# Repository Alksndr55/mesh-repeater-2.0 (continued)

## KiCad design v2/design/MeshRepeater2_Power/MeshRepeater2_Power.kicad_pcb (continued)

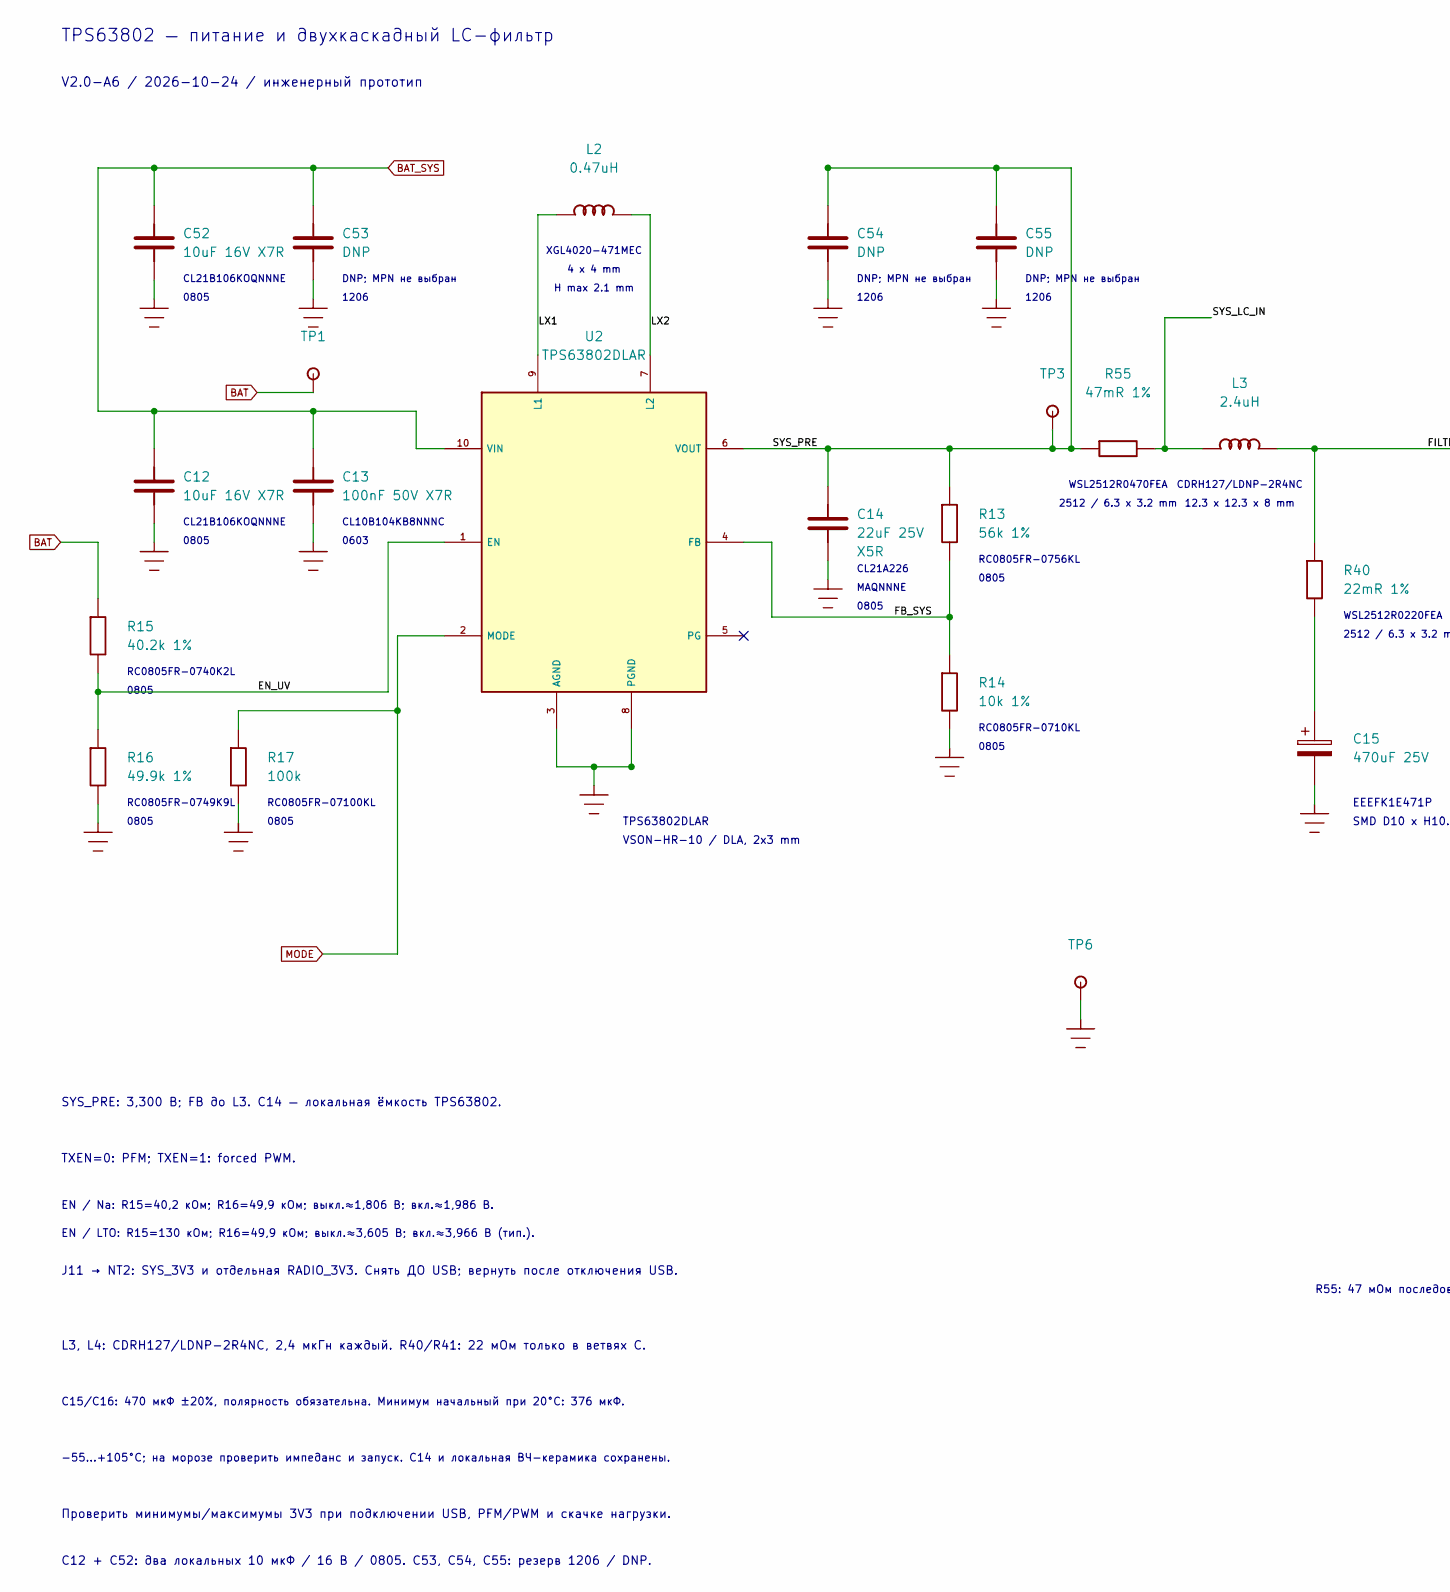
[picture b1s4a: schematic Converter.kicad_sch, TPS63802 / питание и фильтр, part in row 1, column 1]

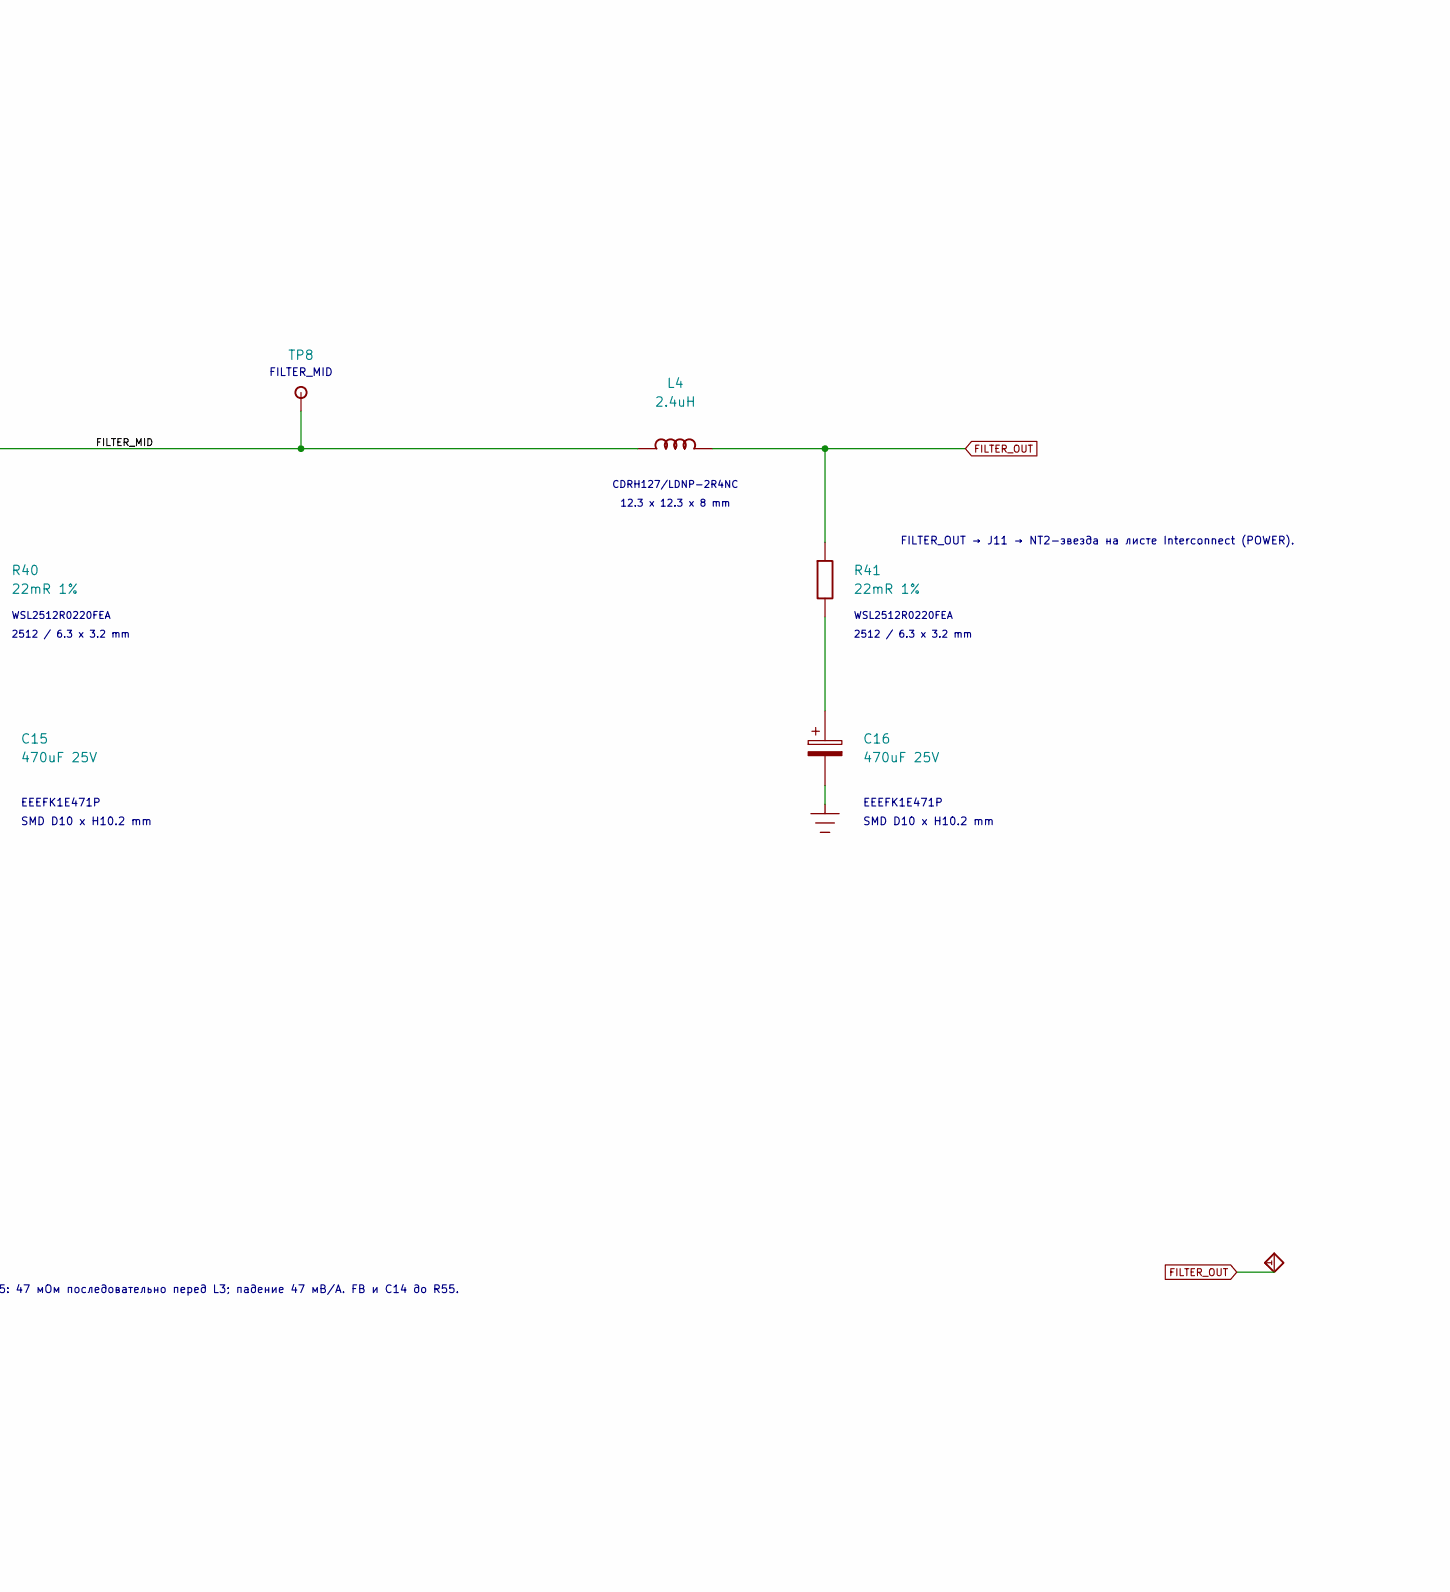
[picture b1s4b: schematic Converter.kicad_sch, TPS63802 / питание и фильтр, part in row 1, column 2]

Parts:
C12: 10uF 16V X7R; C_0805_2012Metric__V2_C12; MPN CL21B106KOQNNNE
C13: 100nF 50V X7R; C_0805_2012Metric; MPN CL21B104KBCNNNC
C14: 22uF 25V X5R; C_0805_2012Metric__V2_C14; MPN CL21A226MAQNNNE
C15, C16: 470uF 25V; CP_Elec_10x10.2; MPN EEEFK1E471P
C52: 10uF 16V X7R; C_0805_2012Metric__V2_C52; MPN CL21B106KOQNNNE
C53: DNP; C_1206_3216Metric__V2_C53
C54: DNP; C_1206_3216Metric__V2_C54
C55: DNP; C_1206_3216Metric__V2_C55
L2: 0.47uH; L_Coilcraft_XGL4020_471MEC_HandSolderUniversal; MPN XGL4020-471MEC; LCSC C5837785
L3: 2.4uH; L_Sumida_CDRH127_LD__V2_L3; MPN CDRH127/LDNP-2R4NC
L4: 2.4uH; L_Sumida_CDRH127_LD__V2_L4; MPN CDRH127/LDNP-2R4NC
R13: 56k 1%; R_0805_2012Metric__V2_R13; MPN RC0805FR-0756KL; LCSC C2523584
R14: 10k 1%; R_0805_2012Metric__V2_R14; MPN RC0805FR-0710KL
R15: 40.2k 1%; R_0805_2012Metric__V2_R15; MPN RC0805FR-0740K2L; LCSC C865475
R16: 49.9k 1%; R_0805_2012Metric__V2_R16; MPN RC0805FR-0749K9L; LCSC C469661
R17: 100k; R_0805_2012Metric__V2_R17; MPN RC0805FR-07100KL
R40: 22mR 1%; R_Vishay_WSL2512_A3__A3_R40; MPN WSL2512R0220FEA; LCSC C4041551
R41: 22mR 1%; R_Vishay_WSL2512_A3__A3_R41; MPN WSL2512R0220FEA; LCSC C4041551
R55: 47mR 1%; R_Vishay_WSL2512_A3__A3_R55; MPN WSL2512R0470FEA
TP1: BAT; TestPoint_Pad_D1p5mm_A3_Edge_R0p9
TP3: SYS_PRE; TestPoint_Pad_D1.5mm__V2_TP3
TP6: GND; TestPoint_Pad_D1p5mm_A3_Edge_R0p9
TP8: FILTER_MID; TestPoint_Pad_D1.5mm__V2_TP8; MPN PCB test pad / not purchased
U2: TPS63802DLAR; TPS63802_DLA0010A__V2_U2; MPN TPS63802DLAR; LCSC C2845237

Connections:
/2. Converter/EN_UV: R15.2, R16.1, U2.1 (EN)
/2. Converter/FB_SYS: R13.2, R14.1, U2.4 (FB)
/2. Converter/FILTER_MID: L3.2, L4.1, R40.1, TP8.1
/2. Converter/LX1: L2.1, U2.9 (L1)
/2. Converter/LX2: L2.2, U2.7 (L2)
/2. Converter/SYS_LC_IN: L3.1, R55.2
/2. Converter/SYS_PRE: C14.1, C54.1, C55.1, R13.1, R55.1, TP3.1, U2.6 (VOUT)
BAT: R15.1, TP1.1; also elsewhere on the board
BAT_SYS: C12.1, C13.1, C52.1, C53.1, U2.10 (VIN); also elsewhere on the board
FILTER_OUT: L4.2, R41.1; also elsewhere on the board
GND: C12.2, C13.2, C14.2, C15.2, C16.2, C52.2, C53.2, C54.2, C55.2, R14.2, R16.2, R17.2, TP6.1, U2.3 (AGND), U2.8 (PGND); also elsewhere on the board
MODE: R17.1, U2.2 (MODE); also elsewhere on the board
unnamed: C15.1, R40.2
unnamed: C16.1, R41.2

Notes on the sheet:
EN / Na: R15=40,2 кОм; R16=49,9 кОм; выкл.≈1,806 В; вкл.≈1,986 В.
Проверить минимумы/максимумы 3V3 при подключении USB, PFM/PWM и скачке нагрузки.
DNP; MPN не выбран
CDRH127/LDNP-2R4NC
L3, L4: CDRH127/LDNP-2R4NC, 2,4 мкГн каждый. R40/R41: 22 мОм только в ветвях C.
CL21A226
0805
RC0805FR-0756KL
C12 + C52: два локальных 10 мкФ / 16 В / 0805. C53, C54, C55: резерв 1206 / DNP.
VSON-HR-10 / DLA, 2x3 mm
1206
12.3 x 12.3 x 8 mm
CL10B104KB8NNNC
TPS63802 — питание и двухкаскадный LC-фильтр
R55: 47 мОм последовательно перед L3; падение 47 мВ/А. FB и C14 до R55.
H max 2.1 mm
J11 → NT2: SYS_3V3 и отдельная RADIO_3V3. Снять ДО USB; вернуть после отключения USB.
WSL2512R0470FEA
CL21B106KOQNNNE
4 x 4 mm
RC0805FR-0710KL
2512 / 6.3 x 3.2 mm
RC0805FR-0740K2L
SYS_PRE: 3,300 В; FB до L3. C14 — локальная ёмкость TPS63802.
FILTER_OUT → J11 → NT2-звезда на листе Interconnect (POWER).
TPS63802DLAR
TXEN=0: PFM; TXEN=1: forced PWM.
V2.0-A6 / 2026-10-24 / инженерный прототип
WSL2512R0220FEA
EN / LTO: R15=130 кОм; R16=49,9 кОм; выкл.≈3,605 В; вкл.≈3,966 В (тип.).
0603
RC0805FR-07100KL
XGL4020-471MEC
MAQNNNE
RC0805FR-0749K9L
FILTER_MID
EEEFK1E471P
SMD D10 x H10.2 mm
C15/C16: 470 мкФ ±20%, полярность обязательна. Минимум начальный при 20°C: 376 мкФ.
−55…+105°C; на морозе проверить импеданс и запуск. C14 и локальная ВЧ-керамика сохранены.

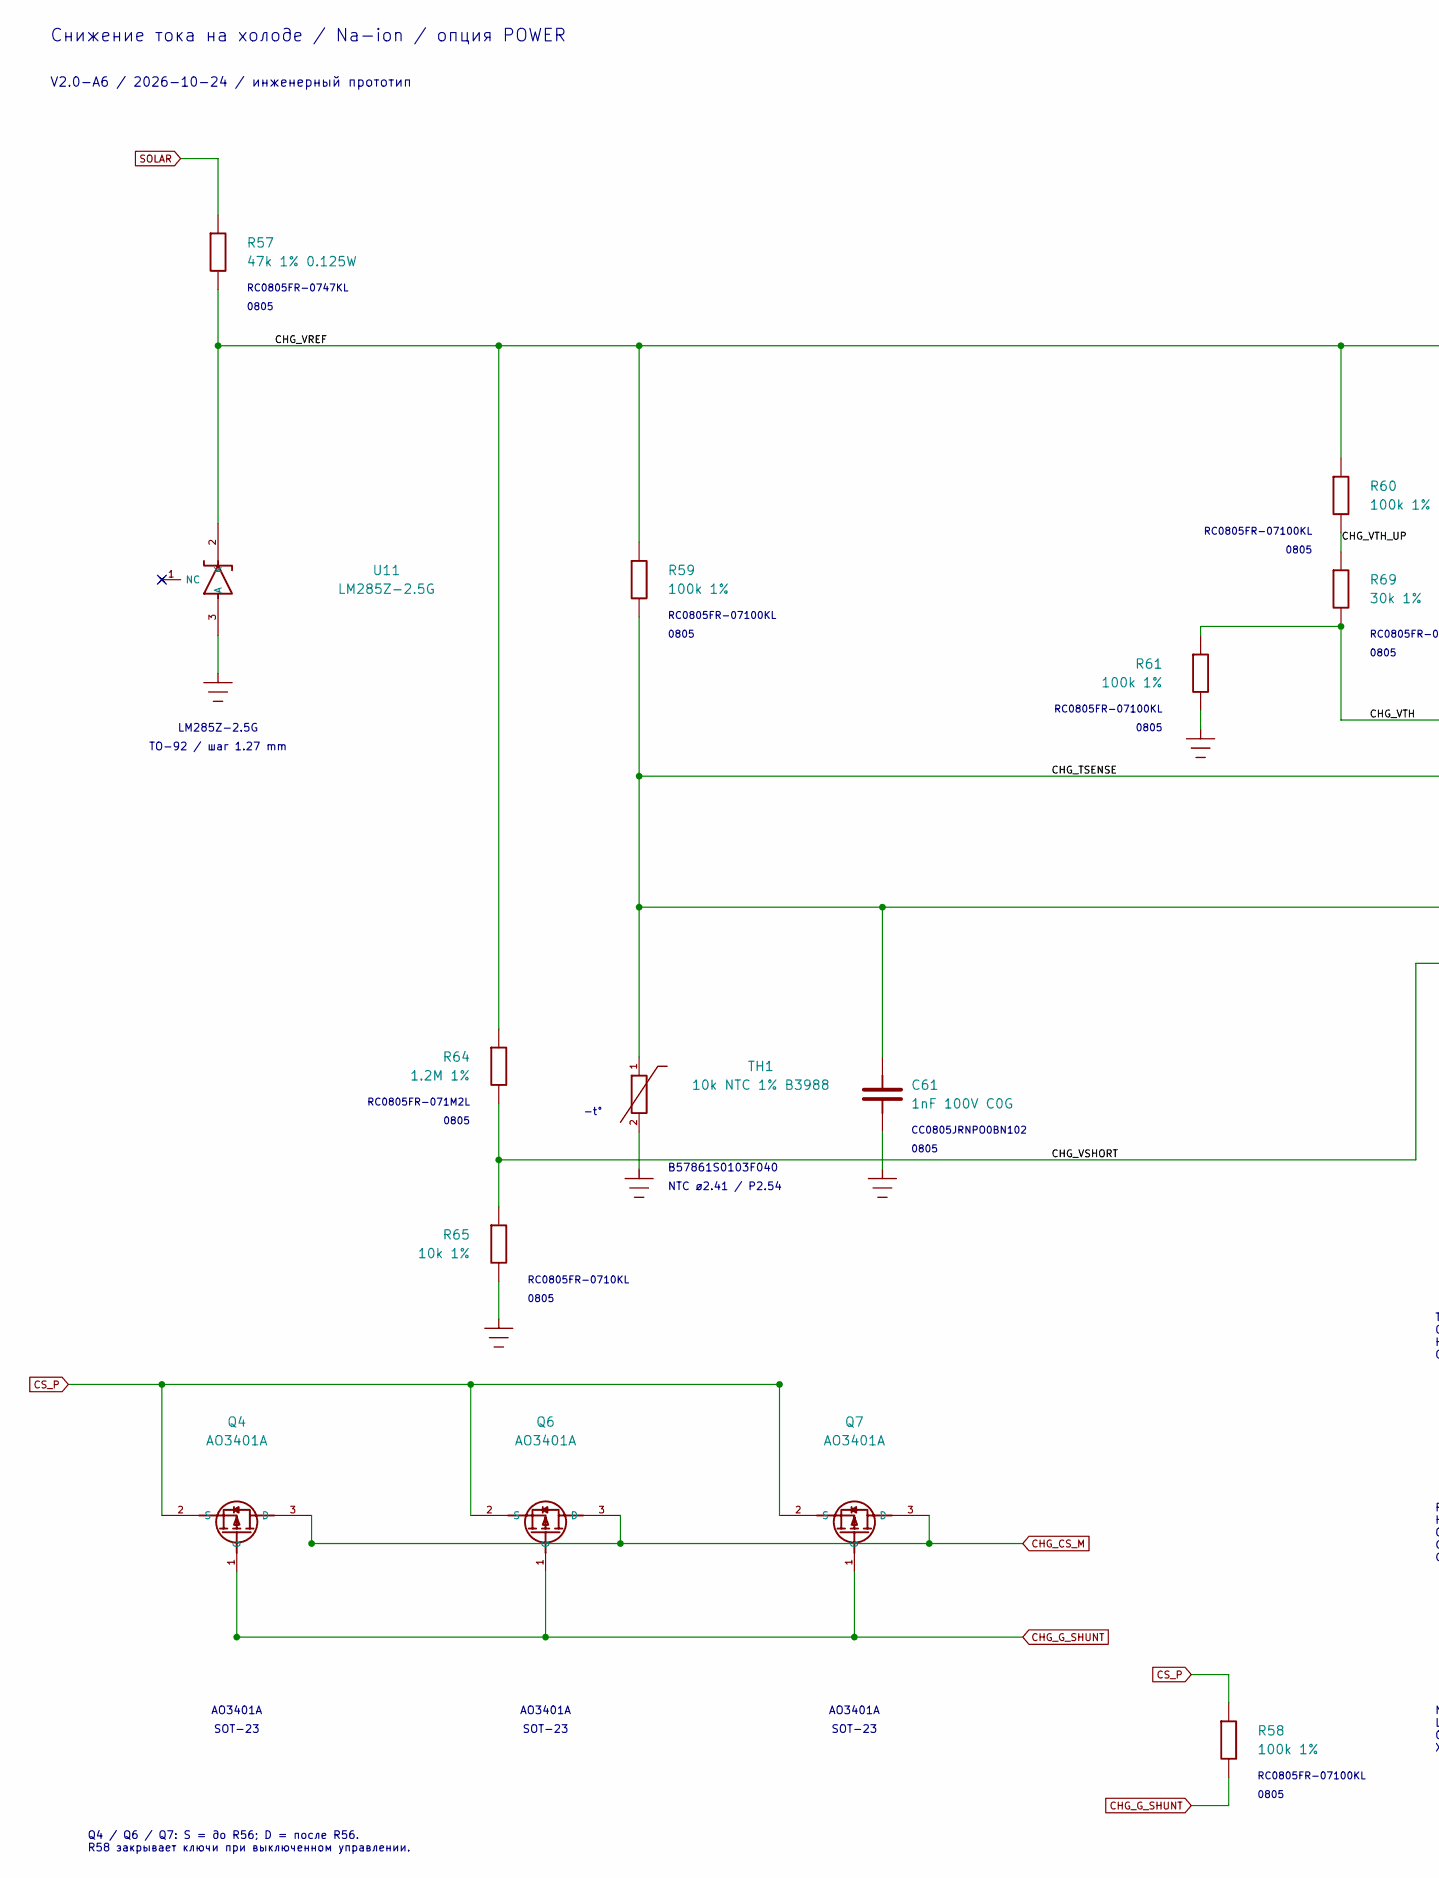
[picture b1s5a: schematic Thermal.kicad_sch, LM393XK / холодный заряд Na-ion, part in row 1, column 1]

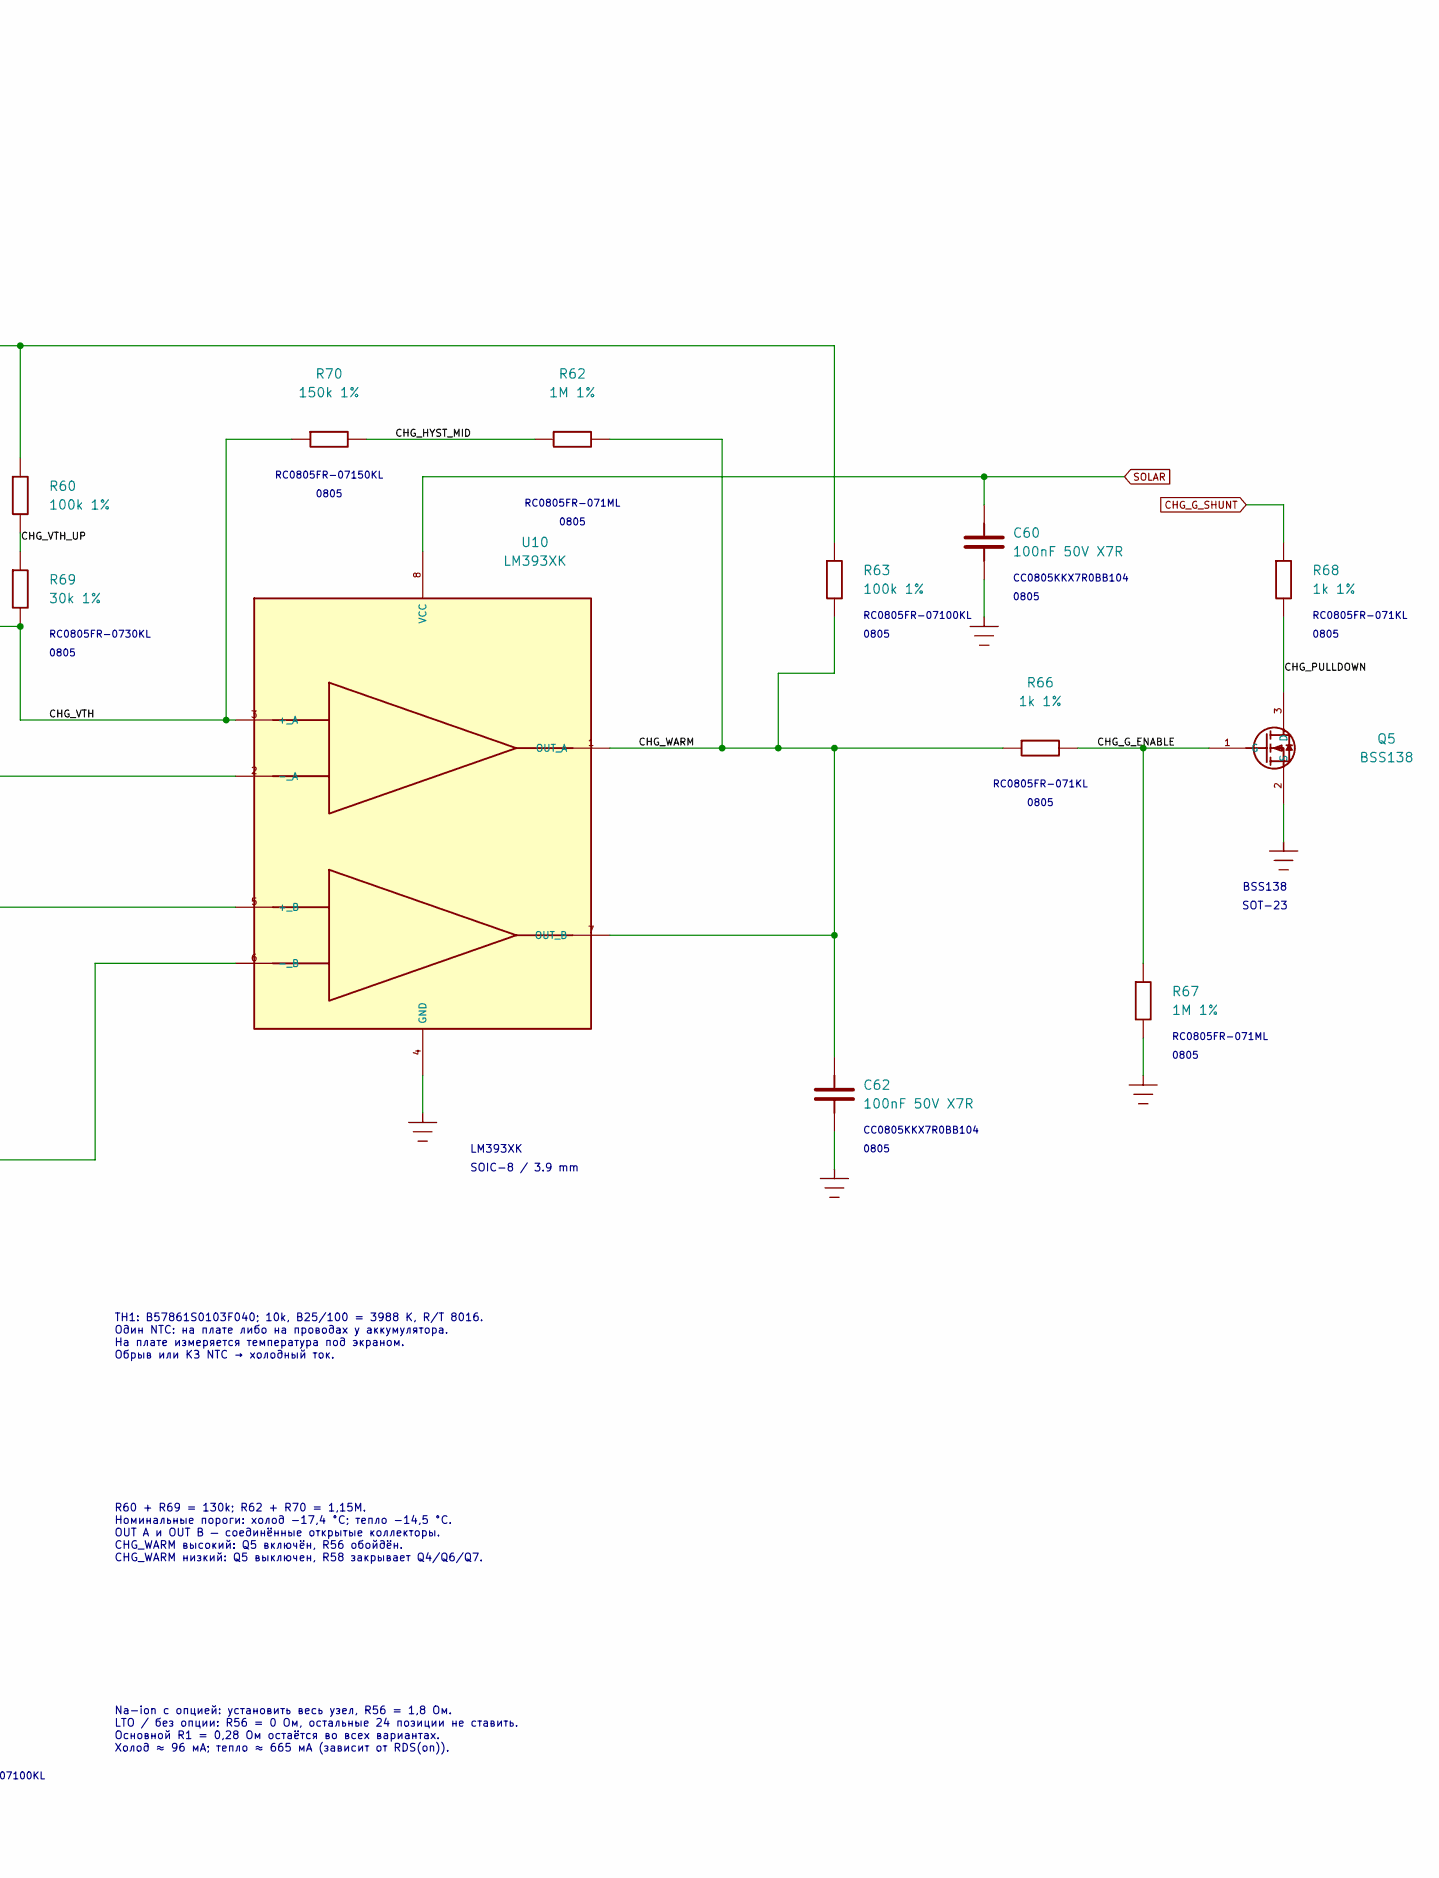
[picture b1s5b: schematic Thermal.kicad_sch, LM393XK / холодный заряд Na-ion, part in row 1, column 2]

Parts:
C60: 100nF 50V X7R; C_0805_2012Metric__V2_C60; MPN CL21B104KBCNNNC
C61: 1nF 100V C0G; C_0805_2012Metric__V2_C61; MPN CC0805JRNPO0BN102
C62: 100nF 50V X7R; C_0805_2012Metric__V2_C62; MPN CL21B104KBCNNNC
Q4: AO3401A; SOT-23__V2_Q4; MPN AO3401A
Q5: BSS138; SOT-23__V2_Q5; MPN BSS138
Q6: AO3401A; SOT-23__V2_Q6; MPN AO3401A
Q7: AO3401A; SOT-23__V2_Q7; MPN AO3401A
R57: 47k 1% 0.125W; R_0805_2012Metric__V2_R57; MPN RC0805FR-0747KL
R58: 100k 1%; R_0805_2012Metric__V2_R58; MPN RC0805FR-07100KL
R59: 100k 1%; R_0805_2012Metric__V2_R59; MPN RC0805FR-07100KL
R60: 100k 1%; R_0805_2012Metric__V2_R60; MPN RC0805FR-07100KL
R61: 100k 1%; R_0805_2012Metric__V2_R61; MPN RC0805FR-07100KL
R62: 1M 1%; R_0805_2012Metric__V2_R62; MPN RC0805FR-071ML
R63: 100k 1%; R_0805_2012Metric__V2_R63; MPN RC0805FR-07100KL
R64: 1.2M 1%; R_0805_2012Metric__V2_R64; MPN RC0805FR-071M2L
R65: 10k 1%; R_0805_2012Metric__V2_R65; MPN RC0805FR-0710KL
R66: 1k 1%; R_0805_2012Metric__V2_R66; MPN RC0805FR-071KL
R67: 1M 1%; R_0805_2012Metric__V2_R67; MPN RC0805FR-071ML
R68: 1k 1%; R_0805_2012Metric__V2_R68; MPN RC0805FR-071KL
R69: 30k 1%; R_0805_2012Metric__V2_R69; MPN RC0805FR-0730KL
R70: 150k 1%; R_0805_2012Metric__V2_R70; MPN RC0805FR-07150KL
TH1: 10k NTC 1% B3988; NTC_TDK_B57861S_Onboard_or_Remote_P2.54mm__V2_TH1; MPN B57861S0103F040
U10: LM393XK; SOIC-8_3.9x4.9mm_P1.27mm__V2_U10; MPN LM393XK
U11: LM285Z-2.5G; TO-92_Inline__V2_U11; MPN LM285Z-2.5G

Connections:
/4. Thermal/CHG_G_ENABLE: Q5.1, R66.2, R67.1
/4. Thermal/CHG_HYST_MID: R62.2, R70.1
/4. Thermal/CHG_PULLDOWN: Q5.3, R68.2
/4. Thermal/CHG_TSENSE: C61.1, R59.2, TH1.1, U10.2, U10.5
/4. Thermal/CHG_VREF: R57.2, R59.1, R60.1, R63.1, R64.1, U11.2
/4. Thermal/CHG_VSHORT: R64.2, R65.1, U10.6
/4. Thermal/CHG_VTH: R61.1, R69.2, R70.2, U10.3
/4. Thermal/CHG_VTH_UP: R60.2, R69.1
/4. Thermal/CHG_WARM: C62.1, R62.1, R63.2, R66.1, U10.1, U10.7
CHG_CS_M: Q4.3, Q6.3, Q7.3; also elsewhere on the board
CHG_G_SHUNT: Q4.1, Q6.1, Q7.1, R58.2, R68.1
CS_P: Q4.2, Q6.2, Q7.2, R58.1; also elsewhere on the board
GND: C60.2, C61.2, C62.2, Q5.2, R61.2, R65.2, R67.2, TH1.2, U10.4, U11.3; also elsewhere on the board
SOLAR: C60.1, R57.1, U10.8; also elsewhere on the board

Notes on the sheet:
0805
RC0805FR-071ML
Na-ion с опцией: установить весь узел, R56 = 1,8 Ом. LTO / без опции: R56 = 0 Ом, остальные 24 позиции не ставить. Основной R1 = 0,28 Ом остаётся во всех вариантах. Холод ≈ 96 мА; тепло ≈ 665 мА (зависит от RDS(on)).
CC0805KKX7R0BB104
Снижение тока на холоде / Na-ion / опция POWER
RC0805FR-07100KL
AO3401A
V2.0-A6 / 2026-10-24 / инженерный прототип
Q4 / Q6 / Q7: S = до R56; D = после R56. R58 закрывает ключи при выключенном управлении.
SOT-23
RC0805FR-0710KL
TO-92 / шаг 1.27 mm
LM285Z-2.5G
SOIC-8 / 3.9 mm
TH1: B57861S0103F040; 10k, B25/100 = 3988 K, R/T 8016. Один NTC: на плате либо на проводах у аккумулятора. На плате измеряется температура под экраном. Обрыв или КЗ NTC → холодный ток.
LM393XK
BSS138
R60 + R69 = 130k; R62 + R70 = 1,15M. Номинальные пороги: холод −17,4 °C; тепло −14,5 °C. OUT A и OUT B — соединённые открытые коллекторы. CHG_WARM высокий: Q5 включён, R56 обойдён. CHG_WARM низкий: Q5 выключен, R58 закрывает Q4/Q6/Q7.
RC0805FR-071KL
RC0805FR-0730KL
NTC ø2.41 / P2.54
-t°
RC0805FR-0747KL
CC0805JRNPO0BN102
RC0805FR-07150KL
B57861S0103F040
RC0805FR-071M2L

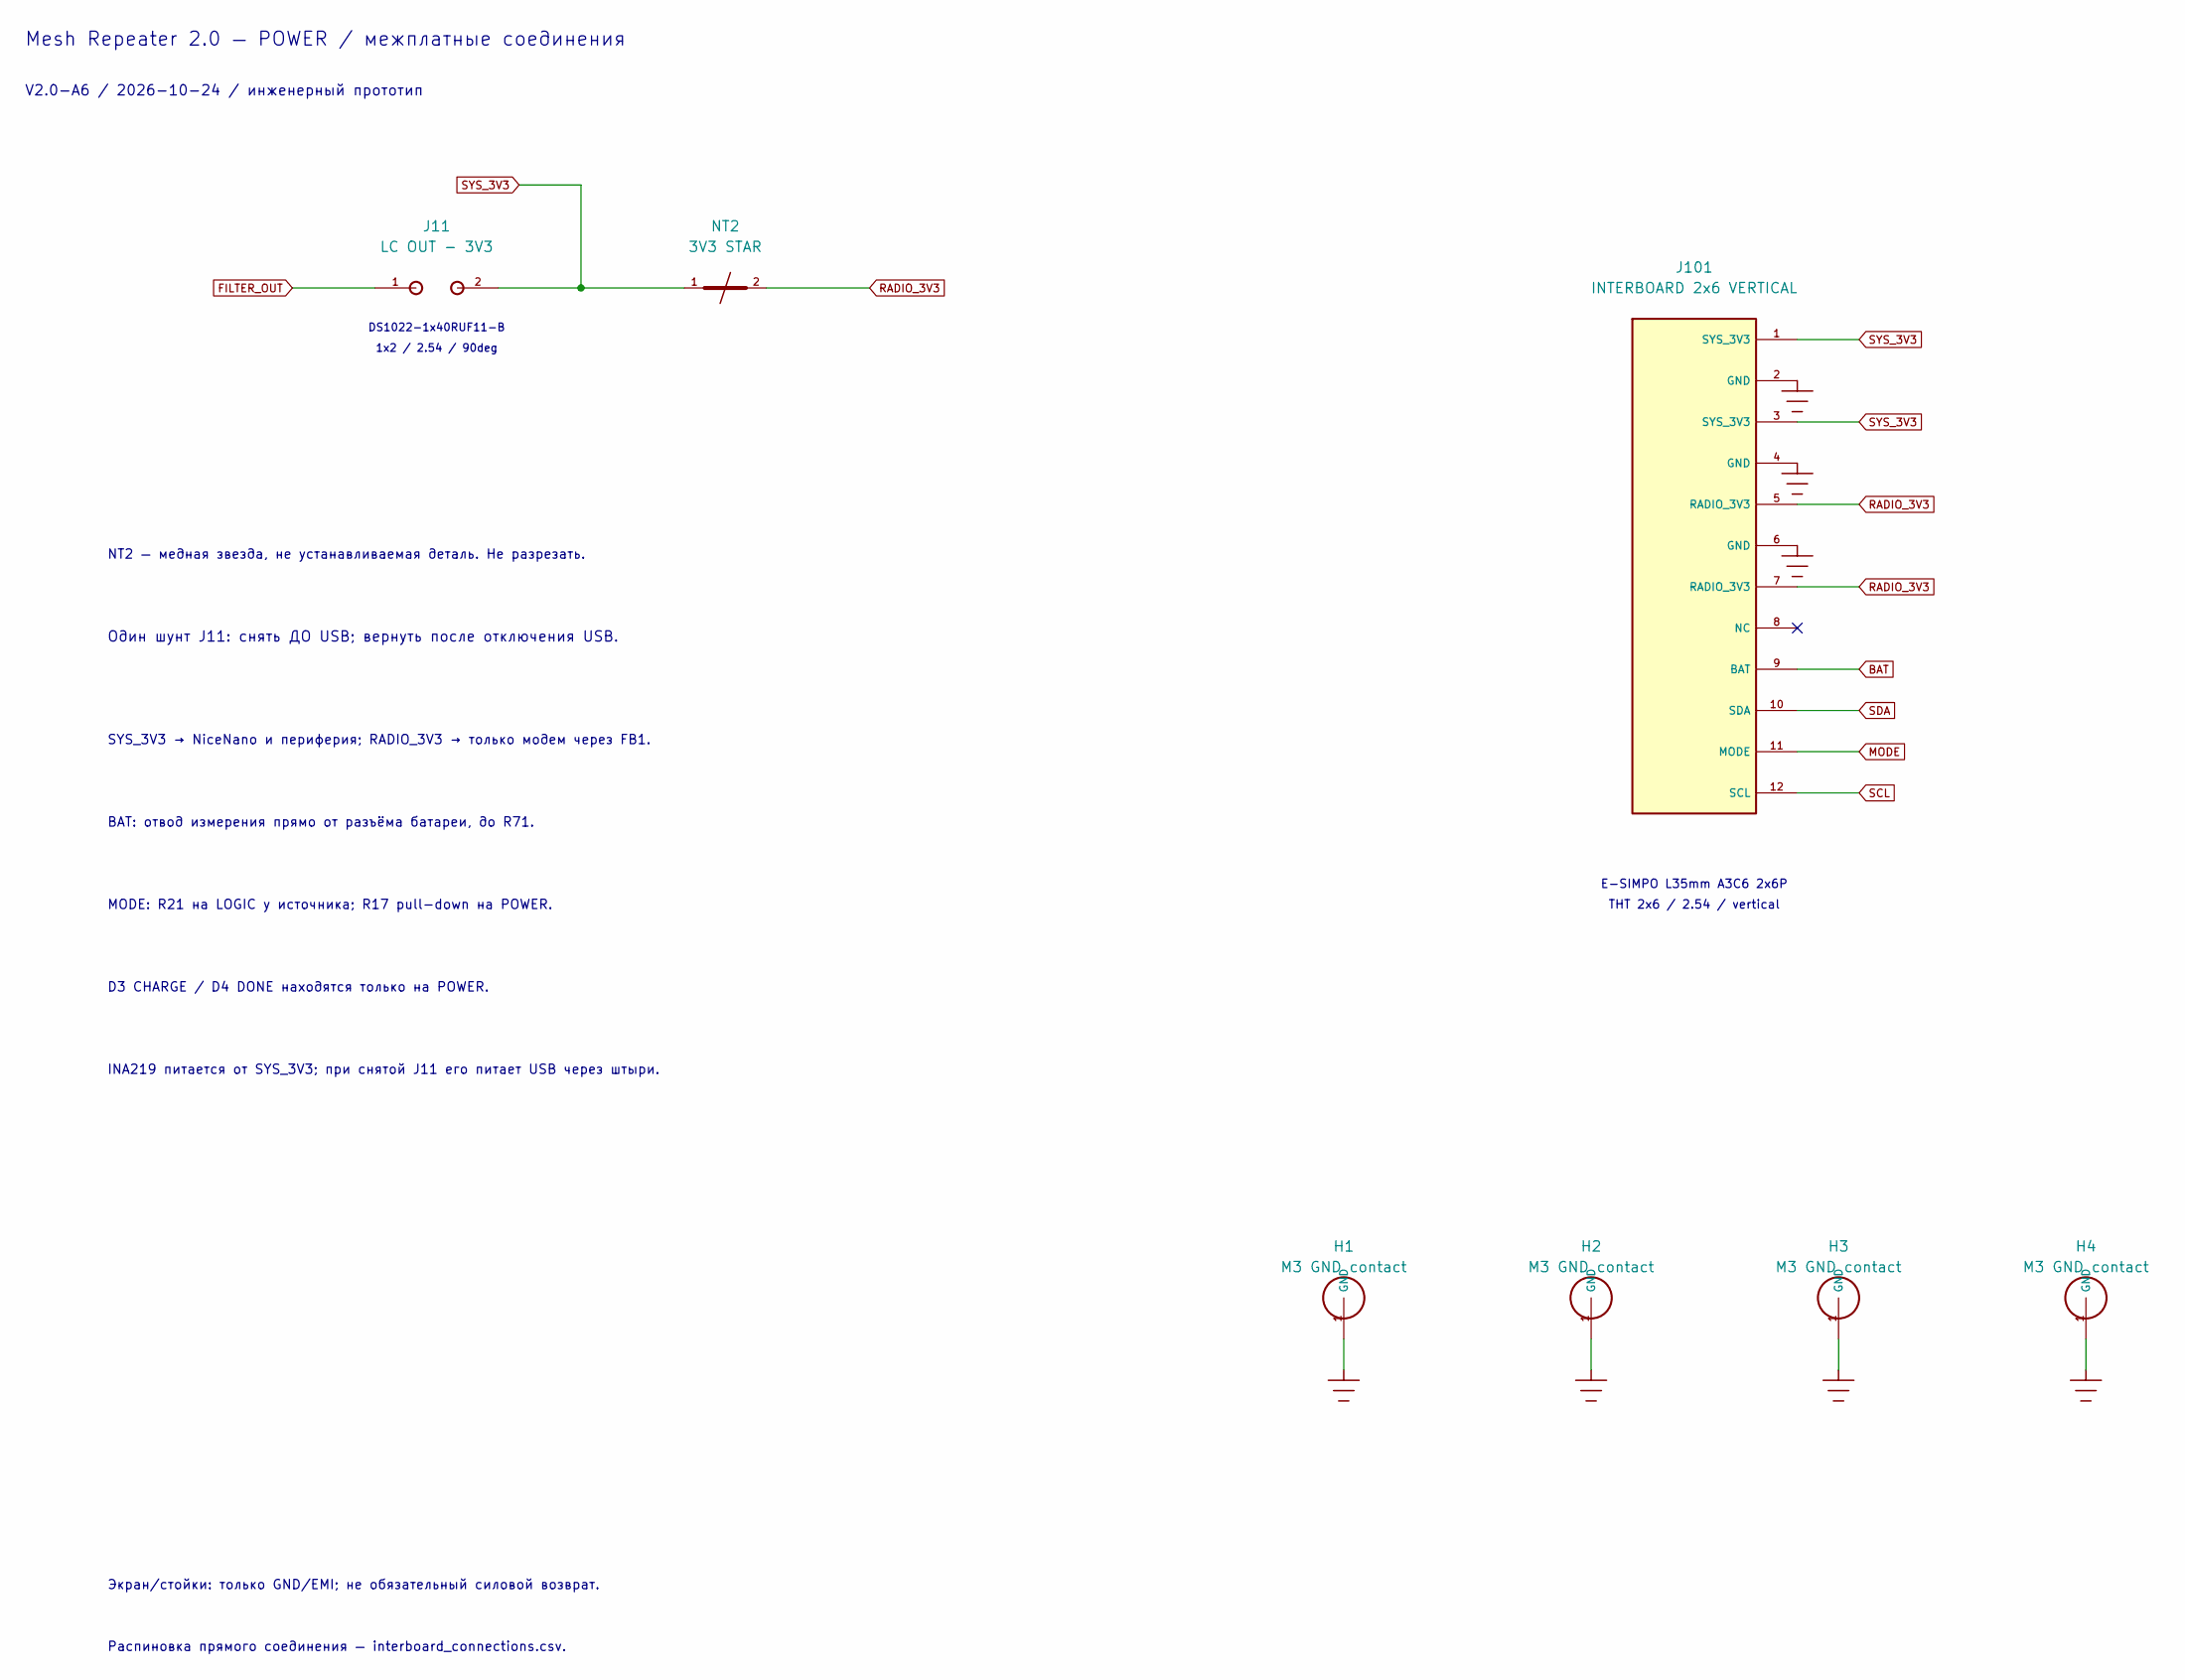
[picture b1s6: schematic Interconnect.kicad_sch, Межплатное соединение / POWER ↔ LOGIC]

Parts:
H1: M3 GND contact; GND_M3_D3.2_OD6__V2_H1; MPN PCB land M3 GND OD6 drill3.2
H2: M3 GND contact; GND_M3_D3.2_OD6__V2_H2; MPN PCB land M3 GND OD6 drill3.2
H3: M3 GND contact; GND_M3_D3.2_OD6__V2_H3; MPN PCB land M3 GND OD6 drill3.2
H4: M3 GND contact; GND_M3_D3.2_OD6__V2_H4; MPN PCB land M3 GND OD6 drill3.2
J11: LC OUT - 3V3; Connfly_DS1022_1x02RUF11_B_Horizontal; MPN Connfly DS1022-1x40RUF11-B cut to2pins
J101: INTERBOARD 2x6 VERTICAL; Ali_PinHeader_2x06_P2.54_L35_A3C6__V2_J101; MPN E-SIMPO L35mm A3C6 2x6P
NT2: 3V3 STAR; NetTie_2_SMD_Power_Star_A3

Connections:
BAT: J101.9 (BAT); also elsewhere on the board
FILTER_OUT: J11.1; also elsewhere on the board
GND: H1.1, H2.1, H3.1, H4.1, J101.2 (GND), J101.4 (GND), J101.6 (GND); also elsewhere on the board
MODE: J101.11 (MODE); also elsewhere on the board
RADIO_3V3: J101.5 (RADIO_3V3), J101.7 (RADIO_3V3), NT2.2
SCL: J101.12 (SCL); also elsewhere on the board
SDA: J101.10 (SDA); also elsewhere on the board
SYS_3V3: J11.2, J101.1 (SYS_3V3), J101.3 (SYS_3V3), NT2.1; also elsewhere on the board

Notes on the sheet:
E-SIMPO L35mm A3C6 2x6P
NT2 — медная звезда, не устанавливаемая деталь. Не разрезать.
BAT: отвод измерения прямо от разъёма батареи, до R71.
INA219 питается от SYS_3V3; при снятой J11 его питает USB через штыри.
D3 CHARGE / D4 DONE находятся только на POWER.
1x2 / 2.54 / 90deg
DS1022-1x40RUF11-B
V2.0-A6 / 2026-10-24 / инженерный прототип
THT 2x6 / 2.54 / vertical
Экран/стойки: только GND/EMI; не обязательный силовой возврат.
Mesh Repeater 2.0 — POWER / межплатные соединения
MODE: R21 на LOGIC у источника; R17 pull-down на POWER.
Один шунт J11: снять ДО USB; вернуть после отключения USB.
Распиновка прямого соединения — interboard_connections.csv.
SYS_3V3 → NiceNano и периферия; RADIO_3V3 → только модем через FB1.

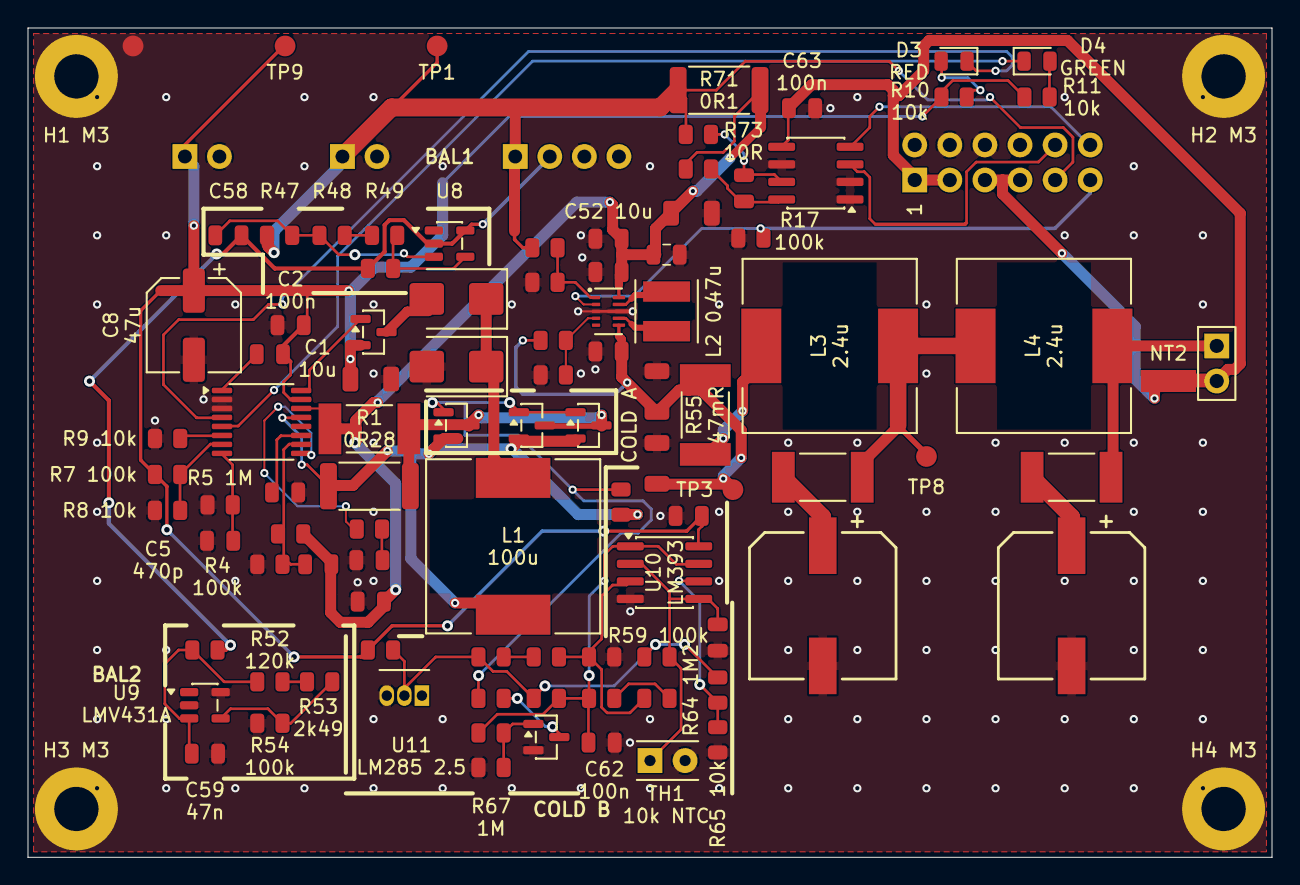
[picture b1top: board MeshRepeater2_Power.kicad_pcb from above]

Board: 2 copper layers, 90.0 x 60.0 mm, 105 parts (0 on the bottom side), 55 nets.
